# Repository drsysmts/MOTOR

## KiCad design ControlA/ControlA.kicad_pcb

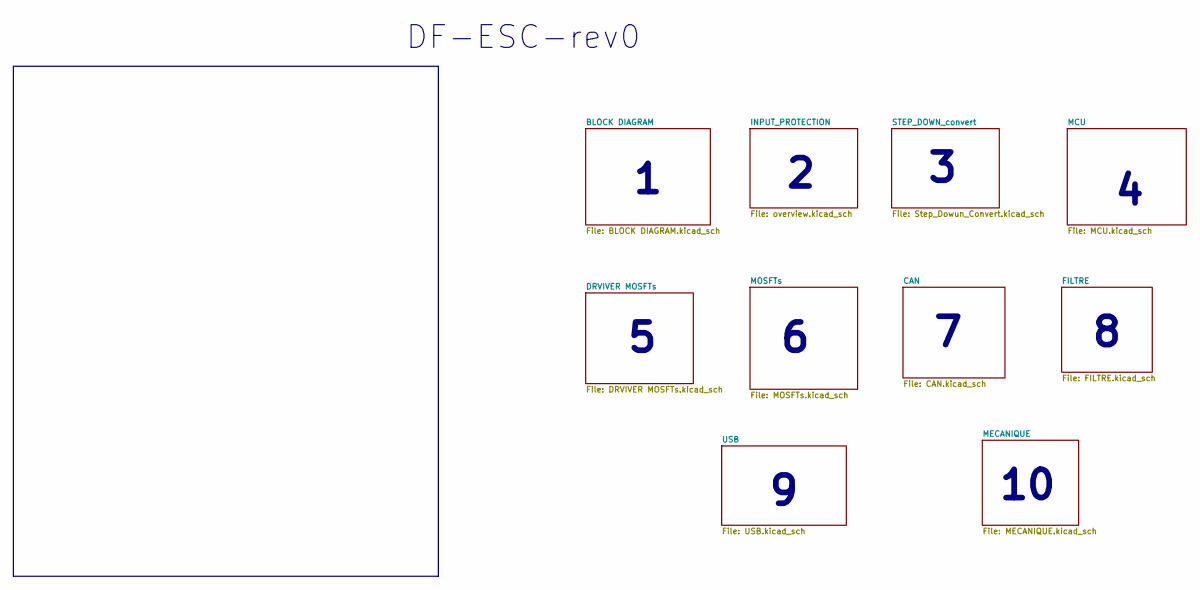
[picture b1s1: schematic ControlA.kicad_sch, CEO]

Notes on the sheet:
DF-ESC-rev0

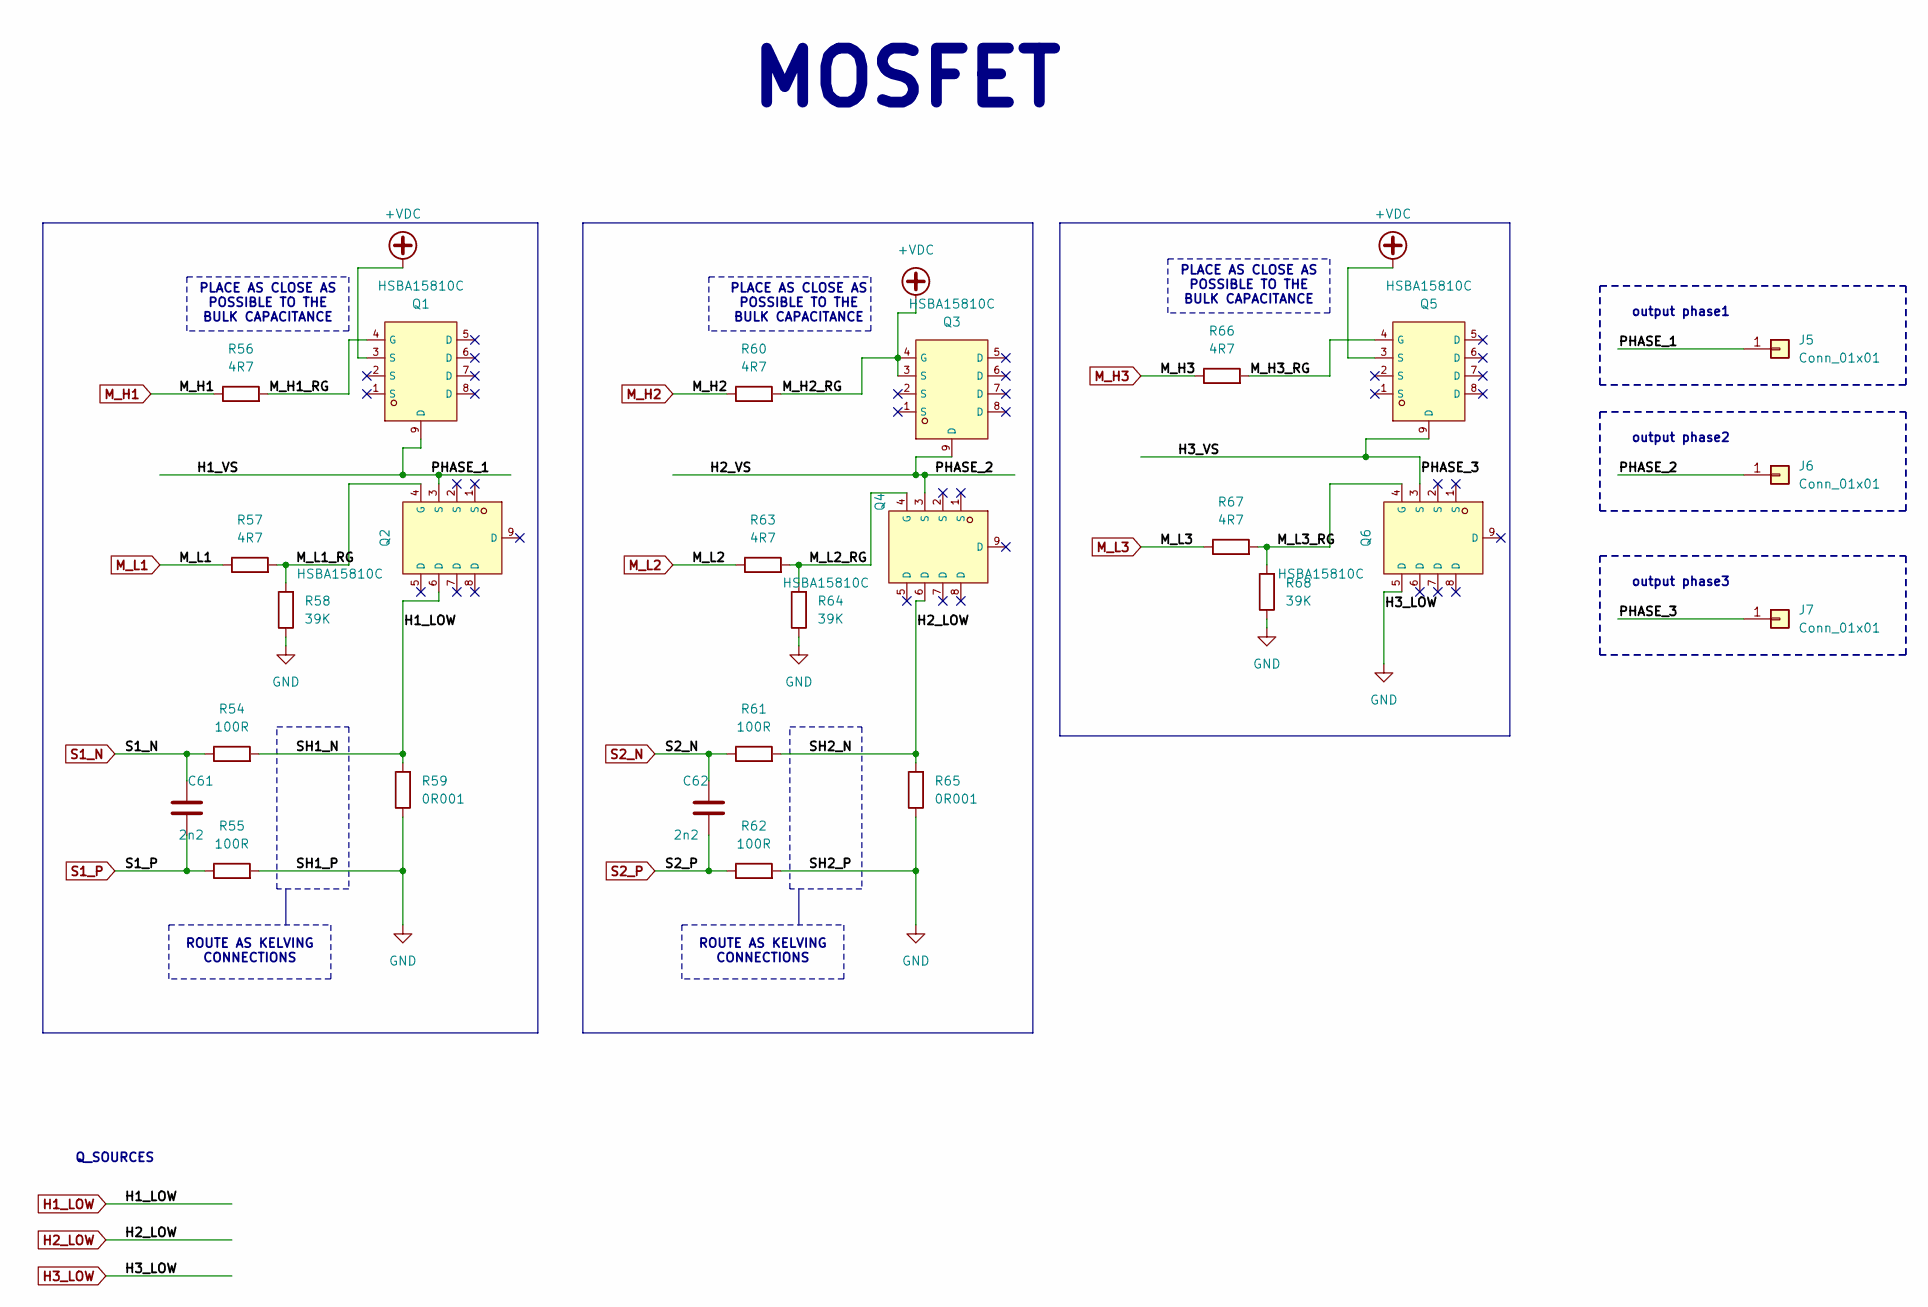
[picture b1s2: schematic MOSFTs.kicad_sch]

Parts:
C61, C62: 2n2; C_0603_1608Metric
J5, J6, J7: Conn_01x01; 7461097
Q1, Q2, Q3, Q4, Q5, Q6: HSBA15810C; PQFN-8_L6.0-W5.0-P1.27-LS6.0-BL; LCSC C845605
R54, R55, R61, R62: 100R; R_0805_2012Metric
R56, R57, R60, R63, R66, R67: 4R7; R_0805_2012Metric
R58, R64, R68: 39K; R_0805_2012Metric
R59, R65: 0R001; R_0805_2012Metric

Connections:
+VDC: Q1.3 (S), Q3.3 (S), Q3.4 (G), Q5.3 (S), R60.2; also elsewhere on the board
/MOSFTs/H1_VS: J5.1, Q1.9 (D), Q2.3 (S)
/MOSFTs/H2_VS: J6.1, Q3.9 (D), Q4.3 (S)
/MOSFTs/H3_VS: J7.1, Q5.9 (D), Q6.3 (S)
/MOSFTs/M_H1_RG: Q1.4 (G), R56.2
/MOSFTs/M_H3_RG: Q5.4 (G), R66.2
/MOSFTs/M_L1_RG: Q2.4 (G), R57.2, R58.2
/MOSFTs/M_L2_RG: Q4.4 (G), R63.2, R64.2
/MOSFTs/M_L3_RG: Q6.4 (G), R67.2, R68.2
H1_LOW: Q2.6 (D), R54.2, R59.2; also elsewhere on the board
H2_LOW: Q4.6 (D), R61.2, R65.2; also elsewhere on the board
H3_LOW: Q6.5 (D), R55.2, R58.1, R59.1, R62.2, R64.1, R65.1, R68.1; also elsewhere on the board
M_H1: R56.1; also elsewhere on the board
M_H2: R60.1; also elsewhere on the board
M_H3: R66.1; also elsewhere on the board
M_L1: R57.1; also elsewhere on the board
M_L2: R63.1; also elsewhere on the board
M_L3: R67.1; also elsewhere on the board
S1_N: C61.1, R54.1; also elsewhere on the board
S1_P: C61.2, R55.1; also elsewhere on the board
S2_N: C62.1, R61.1; also elsewhere on the board
S2_P: C62.2, R62.1; also elsewhere on the board

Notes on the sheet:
PLACE AS CLOSE AS POSSIBLE TO THE BULK CAPACITANCE
ROUTE AS KELVING CONNECTIONS
output phase2
output phase3
output phase1
MOSFET
Q_SOURCES

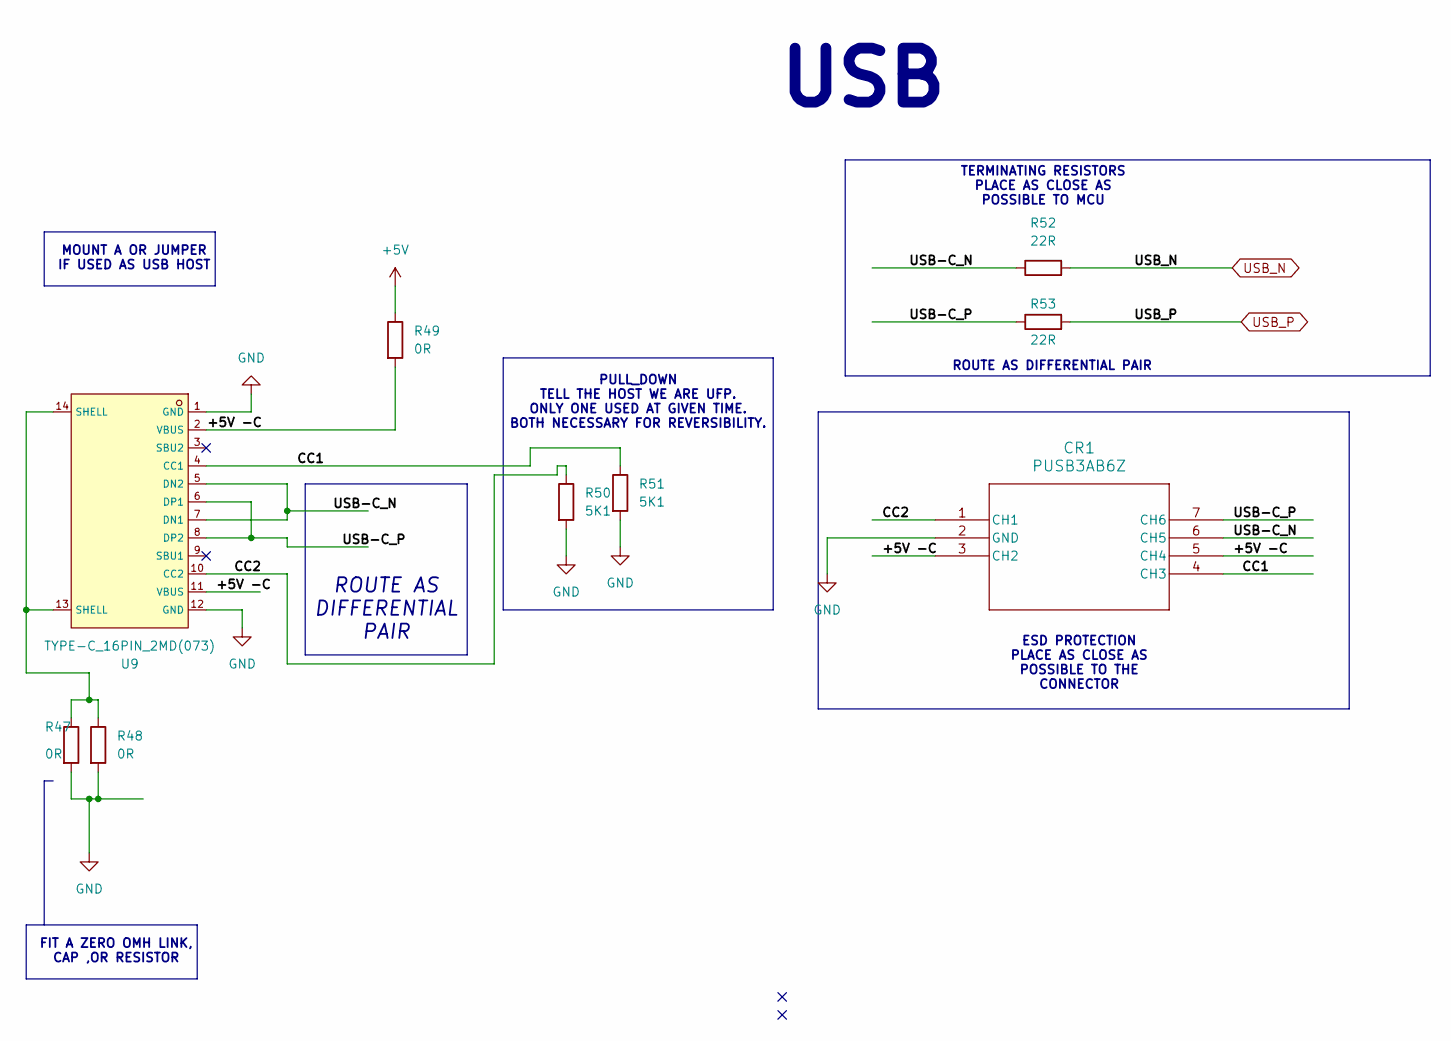
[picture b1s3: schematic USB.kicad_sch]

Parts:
CR1: PUSB3AB6Z; PUSB3AB6Z_NEX-M
R47, R48, R49: 0R; R_0805_2012Metric
R50, R51: 5K1; R_0805_2012Metric
R52, R53: 22R; R_0805_2012Metric
U9: TYPE-C_16PIN_2MD(073); USB-C-SMD_TYPE-C-6PIN-2MD-073; LCSC C2765186

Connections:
+5V: R49.1; also elsewhere on the board
/USB/+5V -C: CR1.3 (CH2), CR1.5 (CH4), R49.2, U9.2 (VBUS), U9.11 (VBUS)
/USB/CC1: CR1.4 (CH3), R51.1, U9.4 (CC1)
/USB/CC2: CR1.1 (CH1), R50.1, U9.10 (CC2)
/USB/USB-C_N: CR1.6 (CH5), R52.1, U9.5 (DN2), U9.7 (DN1)
/USB/USB-C_P: CR1.7 (CH6), R53.1, U9.6 (DP1), U9.8 (DP2)
H3_LOW: CR1.2 (GND), R47.2, R48.2, R50.2, R51.2, U9.1 (GND), U9.12 (GND); also elsewhere on the board
unnamed: R47.1, R48.1, U9.13 (SHELL), U9.14 (SHELL)
USB_N: R52.2; also elsewhere on the board
USB_P: R53.2; also elsewhere on the board

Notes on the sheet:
ROUTE AS DIFFERENTIAL PAIR
MOUNT A OR JUMPER IF USED AS USB HOST
FIT A ZERO OMH LINK, CAP ,OR RESISTOR
ROUTE AS DIFFERENTIAL PAIR
TERMINATING RESISTORS PLACE AS CLOSE AS POSSIBLE TO MCU
PULL_DOWN TELL THE HOST WE ARE UFP. ONLY ONE USED AT GIVEN TIME. BOTH NECESSARY FOR REVERSIBILITY.
ESD PROTECTION PLACE AS CLOSE AS POSSIBLE TO THE CONNECTOR
USB

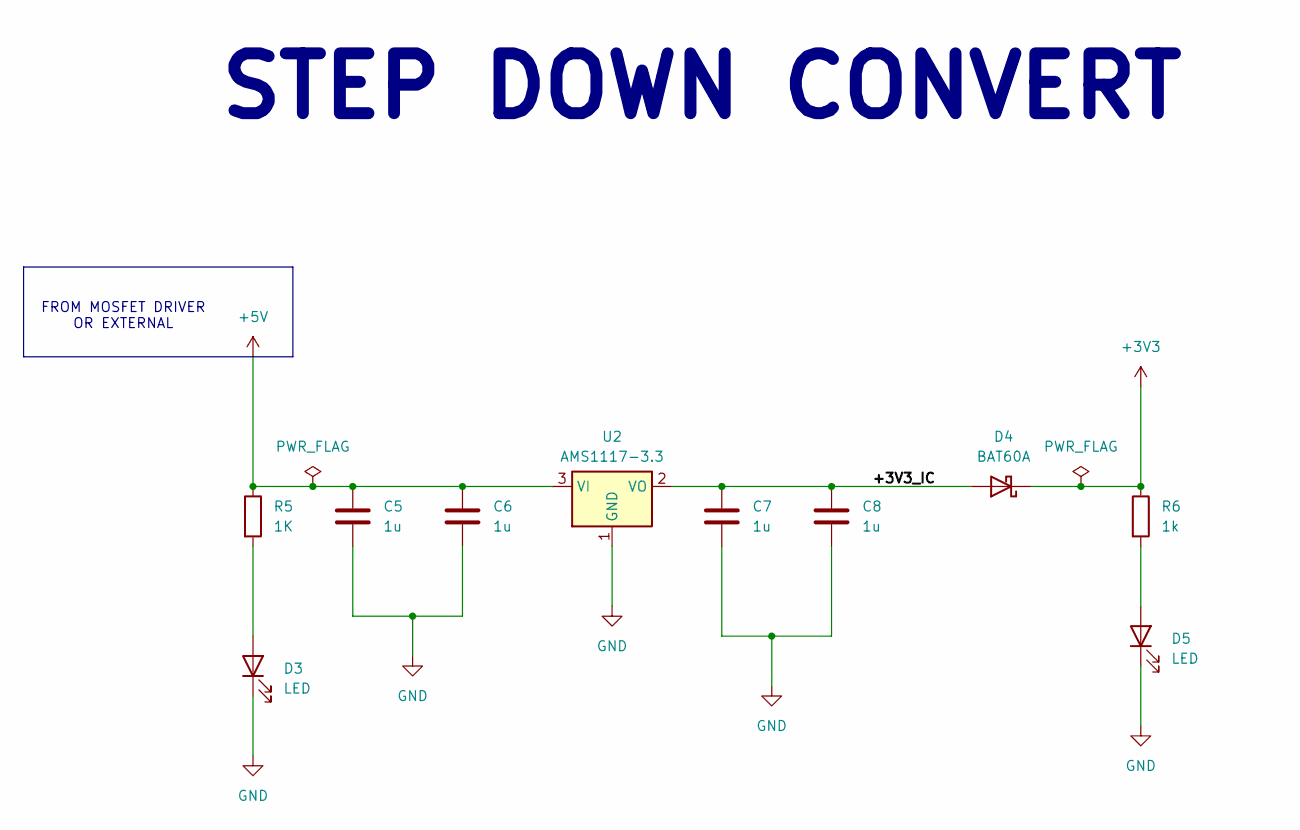
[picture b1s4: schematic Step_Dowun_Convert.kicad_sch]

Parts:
C5, C6, C7, C8: 1u; C_0603_1608Metric
D3, D5: LED; LED0805-R-RD
D4: BAT60A; D_SOD-323
R5: 1K; R_0805_2012Metric
R6: 1k; R_0805_2012Metric
U2: AMS1117-3.3; SOT-223-3_TabPin2

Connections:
+3V3: D4.1 (K), R6.1; also elsewhere on the board
+5V: C5.1, C6.1, R5.1, U2.3 (VI); also elsewhere on the board
/STEP_DOWN_convert/+3V3_IC: C7.1, C8.1, D4.2 (A), U2.2 (VO)
H3_LOW: C5.2, C6.2, C7.2, C8.2, D3.1 (K), D5.1 (K), U2.1 (GND); also elsewhere on the board
unnamed: D3.2 (A), R5.2
unnamed: D5.2 (A), R6.2

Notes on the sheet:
FROM MOSFET DRIVER OR EXTERNAL
STEP DOWN CONVERT

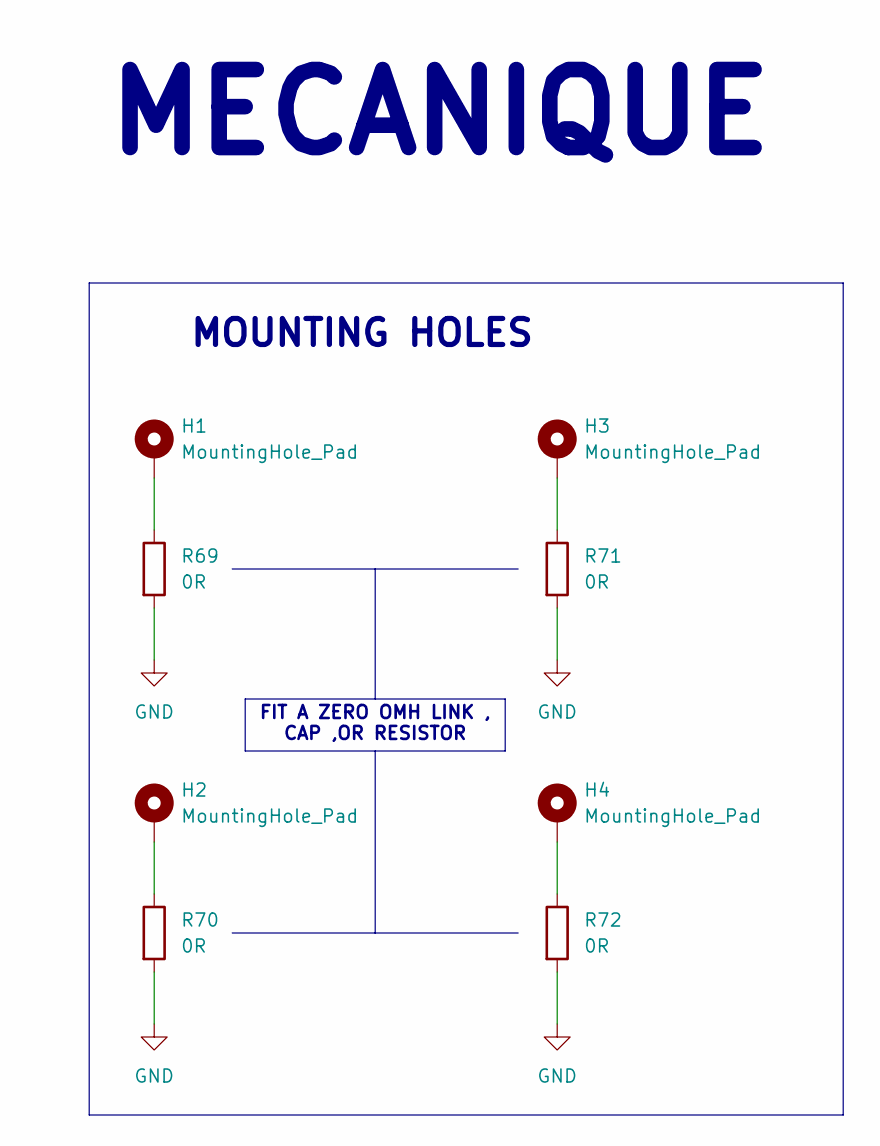
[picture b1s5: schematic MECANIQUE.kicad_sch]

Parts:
H1, H2, H3, H4: MountingHole_Pad; MountingHole_4.3mm_M4_Pad_Via
R69, R70, R71, R72: 0R; R_0805_2012Metric

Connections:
H3_LOW: R69.2, R70.2, R71.2, R72.2; also elsewhere on the board
unnamed: H1.1, R69.1
unnamed: H2.1, R70.1
unnamed: H3.1, R71.1
unnamed: H4.1, R72.1

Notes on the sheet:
MECANIQUE
MOUNTING HOLES
FIT A ZERO OMH LINK , CAP ,OR RESISTOR

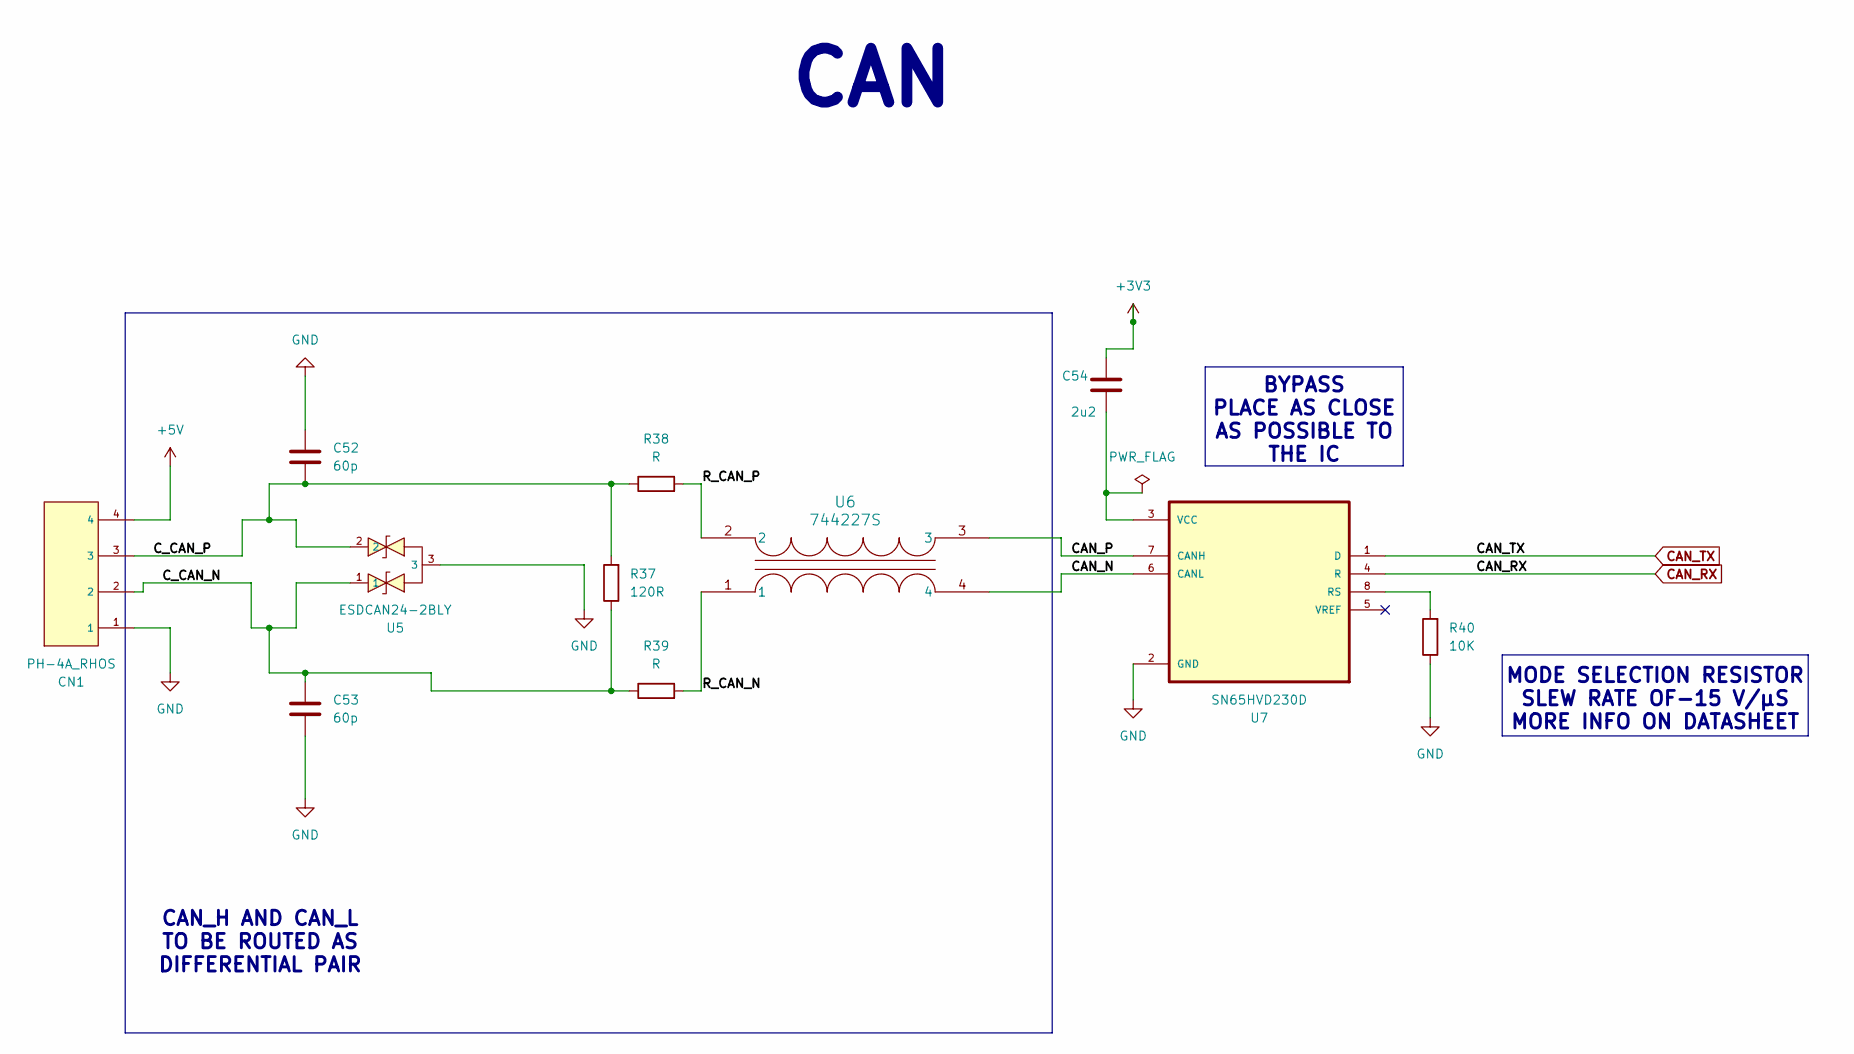
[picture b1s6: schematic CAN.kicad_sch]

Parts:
C52, C53: 60p; C_0603_1608Metric
C54: 2u2; C_0603_1608Metric
CN1: PH-4A_RHOS; CONN-TH_PH-4A; LCSC C2321
R37: 120R; R_0805_2012Metric
R38, R39: R; R_0805_2012Metric
R40: 10K; R_0805_2012Metric
U5: ESDCAN24-2BLY; SOT-23-3_L3.0-W1.7-P0.95-LS2.9-BR; LCSC C246766
U6: 744227S; SMD_227S_WRE-M
U7: SN65HVD230D; SOIC127P599X175-8N

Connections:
+3V3: C54.1; also elsewhere on the board
+5V: CN1.4; also elsewhere on the board
/CAN/CAN_N: U6.4, U7.6 (CANL)
/CAN/CAN_P: U6.3, U7.7 (CANH)
/CAN/C_CAN_N: C53.1, CN1.2, R37.1, R39.1, U5.1
/CAN/C_CAN_P: C52.2, CN1.3, R37.2, R38.1, U5.2
/CAN/R_CAN_N: R39.2, U6.1
/CAN/R_CAN_P: R38.2, U6.2
CAN_RX: U7.4 (R); also elsewhere on the board
CAN_TX: U7.1 (D); also elsewhere on the board
H3_LOW: C52.1, C53.2, CN1.1, R40.1, U5.3, U7.2 (GND); also elsewhere on the board
unnamed: R40.2, U7.8 (RS)
unnamed: C54.2, U7.3 (VCC)

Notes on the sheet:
CAN_H AND CAN_L TO BE ROUTED AS DIFFERENTIAL PAIR
CAN
BYPASS PLACE AS CLOSE AS POSSIBLE TO THE IC
MODE SELECTION RESISTOR SLEW RATE OF-15 V/µS MORE INFO ON DATASHEET

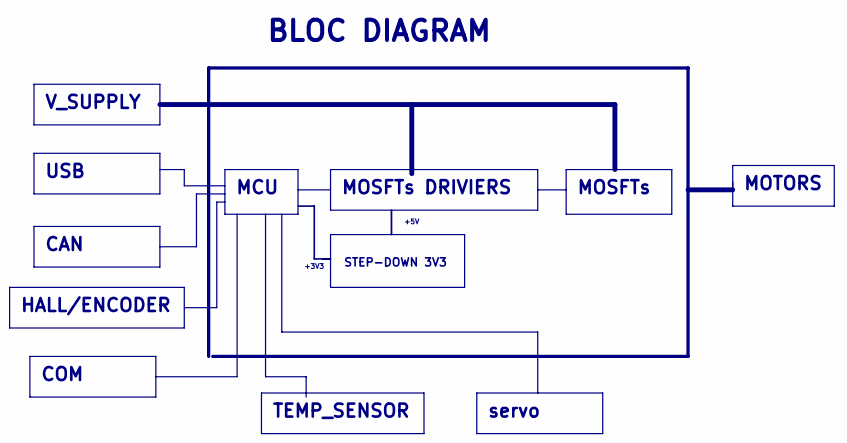
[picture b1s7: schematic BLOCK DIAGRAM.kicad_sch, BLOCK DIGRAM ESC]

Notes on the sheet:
MOSFTs DRIVIERS
CAN
TEMP_SENSOR
HALL/ENCODER
COM
MOTORS
servo
USB
MCU
MOSFTs
V_SUPPLY
+3V3
BLOC DIAGRAM
STEP-DOWN 3V3
+5V

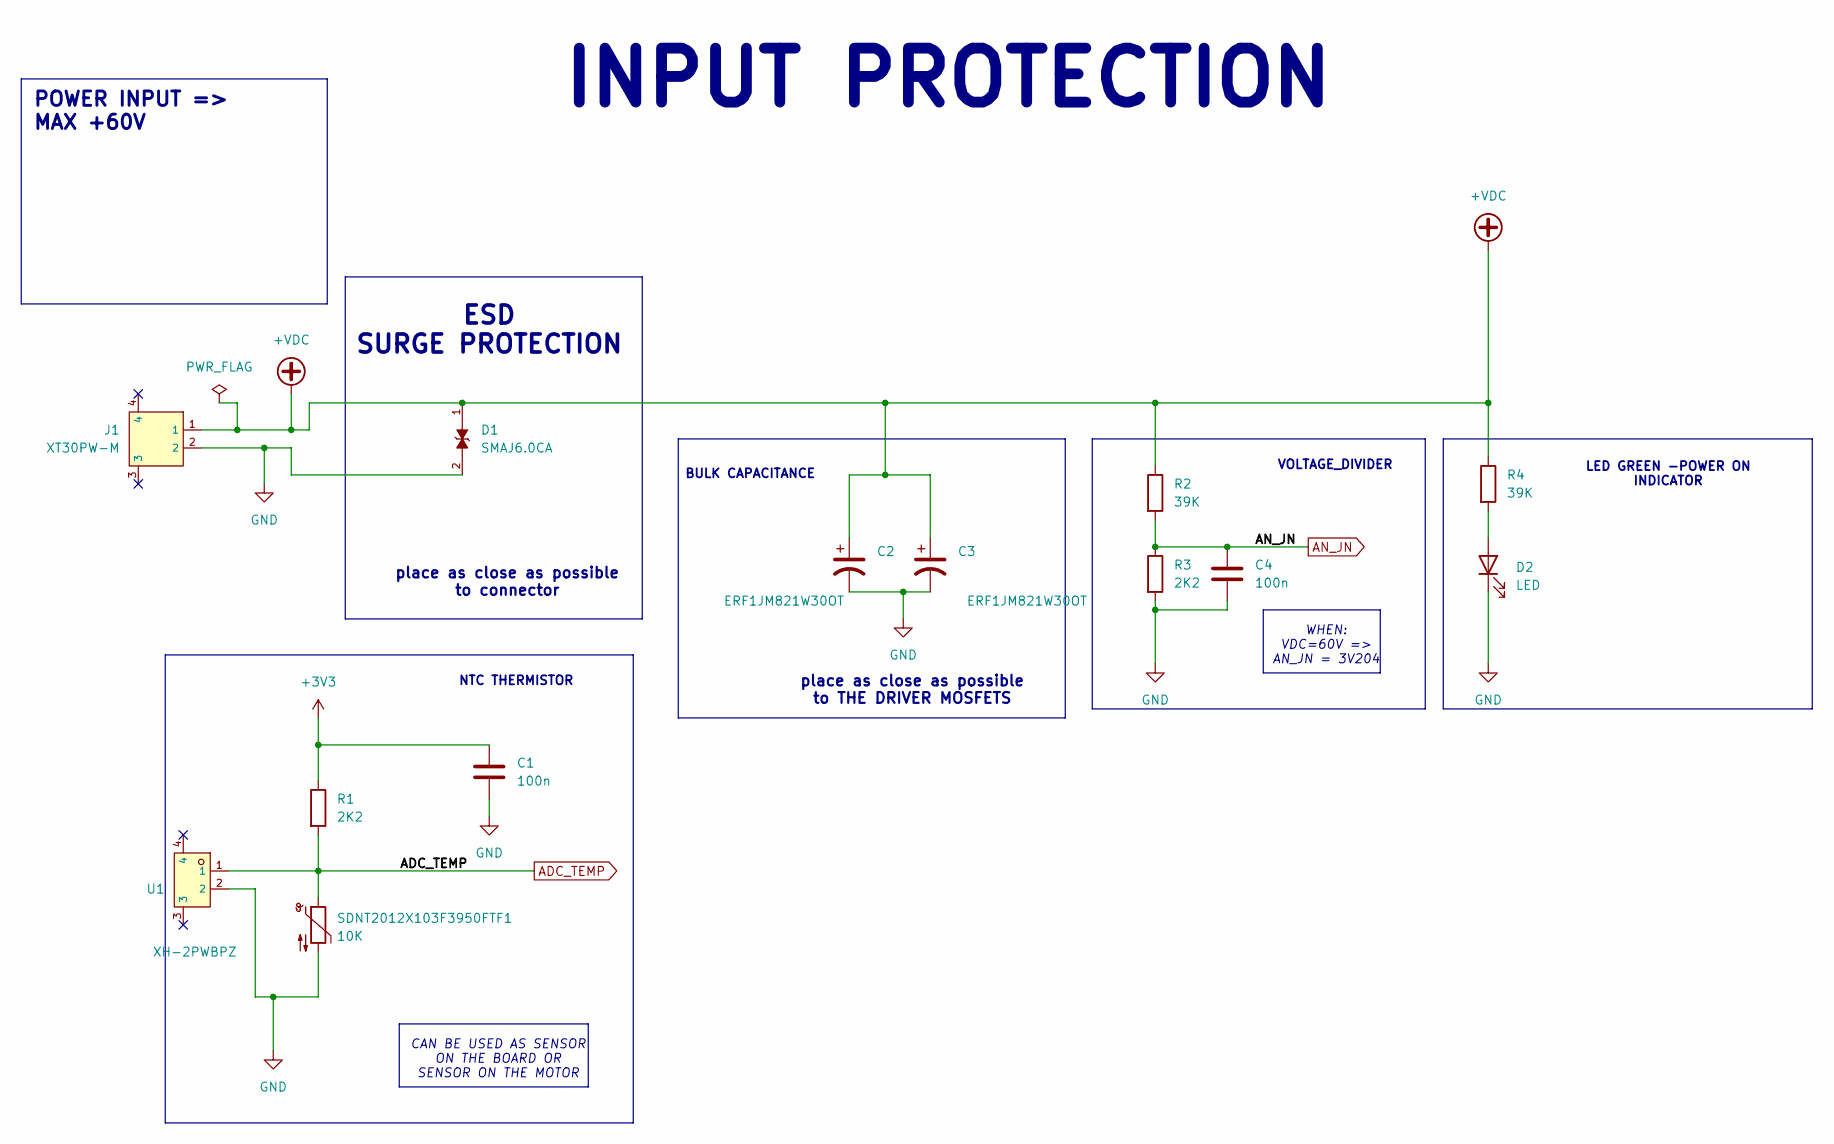
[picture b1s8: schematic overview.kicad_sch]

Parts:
C1: 100n; C_0805_2012Metric
C2, C3: ERF1JM821W30OT; CP_Radial_D12.5mm_P5.00mm
C4: 100n; C_0603_1608Metric
D1: SMAJ6.0CA; DIOM4325X250N; PARTREV S2102
D2: LED; LED0805-R-RD
J1: XT30PW-M; CONN-TH_XT30PW-M; PARTREV 1.2; LCSC C431092
R1, R3: 2K2; R_0805_2012Metric
R2, R4: 39K; R_0805_2012Metric
SDNT2012X103F3950FTF1: 10K; R_0805_2012Metric
U1: XH-2PWBPZ; CONN-SMD_XH-2PWBPZ; LCSC C2687444

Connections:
+3V3: C1.1, R1.1; also elsewhere on the board
+VDC: C2.1, C3.1, D1.1, J1.1, R2.1, R4.1; also elsewhere on the board
ADC_TEMP: R1.2, SDNT2012X103F3950FTF1.1, U1.1
AN_JN: C4.1, R2.2, R3.1
H3_LOW: C1.2, C2.2, C3.2, C4.2, D1.2, D2.1 (K), J1.2, R3.2, SDNT2012X103F3950FTF1.2, U1.2; also elsewhere on the board
unnamed: D2.2 (A), R4.2

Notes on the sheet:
POWER INPUT => MAX +60V
LED GREEN -POWER ON INDICATOR
place as close as possible to connector
ESD SURGE PROTECTION
NTC THERMISTOR
VOLTAGE_DIVIDER
CAN BE USED AS SENSOR ON THE BOARD OR SENSOR ON THE MOTOR
place as close as possible to THE DRIVER MOSFETS
BULK CAPACITANCE
INPUT PROTECTION
WHEN: VDC=60V => AN_JN = 3V204

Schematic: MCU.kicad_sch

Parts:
C9, C10: 100n; C_0603_1608Metric
C11, C12: 10p; C_0603_1608Metric
C13, C14, C15, C16, C17, C18, C20, C22, C23, C24, C25: 100n; C_0402_1005Metric
C19, C21: 2u2; C_0603_1608Metric
D6, D7, D8: LED; LED0805-R-RD
FB1: 120R; L0603
J2: Conn_01x08; PinHeader_1x08_P1.00mm_Vertical
J3: Conn_01x06; PinHeader_1x06_P1.00mm_Vertical
J4: Conn_01x03; PinHeader_1x03_P1.00mm_Vertical
R7: 39K; R_0805_2012Metric
R8, R15, R16: 2K2; R_0805_2012Metric
R9, R14: 0R; R_0805_2012Metric
R10, R11: 0R; R_0402_1005Metric
R12, R13: 1K; R_0805_2012Metric
SDNT2012X103F3950FTF2: 10K; R_0805_2012Metric
SW1: TS-KG87S-AT15F; SW-SMD_4P-L5.2-W5.2-P3.70-LS6.4; LCSC C2874421
U3: STM32F405RGTx; LQFP-64_10x10mm_P0.5mm
Y1: Crystal; Crystal_SMD_5032-2Pin_5.0x3.2mm

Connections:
+3V3: C10.1, C13.1, C14.1, C15.1, C16.1, C17.1, C18.1, C25.1, FB1.2, J2.2, J3.1, R9.2, R14.1, SDNT2012X103F3950FTF2.1, U3.1 (VBAT), U3.19 (VDD), U3.32 (VDD), U3.48 (VDD), U3.64 (VDD); also elsewhere on the board
+5V: J2.1, J4.1; also elsewhere on the board
+VDC: R7.2; also elsewhere on the board
/MCU/ADC_TEMP: R16.2, SDNT2012X103F3950FTF2.2, U3.17 (PA3)
/MCU/AN_JN: C9.1, R7.1, R8.2, U3.10 (PC2)
/MCU/BOOT0_P: R14.2, U3.60 (BOOT0)
/MCU/LED_GREEN: R12.2, U3.24 (PC4)
/MCU/LED_RED: R13.2, U3.25 (PC5)
/MCU/MISQ_ADC_EXT2: J2.7, U3.22 (PA6)
/MCU/NRST: C20.1, J3.5, SW1.3, SW1.4, U3.7 (NRST)
/MCU/PH_0: C11.1, R10.1, Y1.1
/MCU/PH_0_P: R10.2, U3.5 (PH0)
/MCU/PH_1: C12.1, R11.1, Y1.2
/MCU/PH_1_P: R11.2, U3.6 (PH1)
/MCU/SCK_ADC_EXT: J2.4, U3.21 (PA5)
/MCU/SERVO: C24.2, R15.1, U3.57 (PB5)
/MCU/SWCLK: J3.2, U3.49 (PA14)
/MCU/SWDIO: J3.4, U3.46 (PA13)
/MCU/VCAP_1: C19.1, U3.31 (VCAP_1)
/MCU/VCAP_2: C21.1, U3.47 (VCAP_2)
BR_SO1: U3.26 (PB0); also elsewhere on the board
BR_SO2: U3.27 (PB1); also elsewhere on the board
CAN_RX: U3.61 (PB8); also elsewhere on the board
CAN_TX: U3.62 (PB9); also elsewhere on the board
DC_CAL: U3.33 (PB12); also elsewhere on the board
EN_GATE: U3.51 (PC10); also elsewhere on the board
FAULT: U3.53 (PC12); also elsewhere on the board
H1: U3.43 (PA10); also elsewhere on the board
H2: U3.42 (PA9); also elsewhere on the board
H3: U3.41 (PA8); also elsewhere on the board
H3_LOW: C9.2, C10.2, C11.2, C12.2, C13.2, C14.2, C15.2, C16.2, C17.2, C18.2, C19.2, C20.2, C21.2, C22.2, C23.2, C24.1, C25.2, D6.1 (K), D7.1 (K), D8.1 (K), J2.3, J2.8, J3.3, J4.2, R8.1, R16.1, SW1.1, SW1.2, U3.12 (VSSA), U3.18 (VSS), U3.63 (VSS); also elsewhere on the board
HALL1_OUT: U3.58 (PB6); also elsewhere on the board
HALL2_OUT: U3.59 (PB7); also elsewhere on the board
HALL3_OUT: U3.52 (PC11); also elsewhere on the board
L1: U3.36 (PB15); also elsewhere on the board
L2: U3.35 (PB14); also elsewhere on the board
L3: U3.34 (PB13); also elsewhere on the board
unnamed: D6.2 (A), R9.1
unnamed: D7.2 (A), R12.1
unnamed: D8.2 (A), R13.1
unnamed: J4.3, R15.2
unnamed: C22.1, C23.1, FB1.1, U3.13 (VDDA)
RX_SCL_MOSI: J2.6, U3.23 (PA7), U3.29 (PB10), U3.38 (PC7)
SENSE1: U3.16 (PA2); also elsewhere on the board
SENSE2: U3.15 (PA1); also elsewhere on the board
SENSE3: U3.14 (PA0); also elsewhere on the board
TEMP_MOTOR: U3.8 (PC0); also elsewhere on the board
TX_SDA_NSS: J2.5, U3.20 (PA4), U3.30 (PB11), U3.37 (PC6)
USB_N: U3.44 (PA11); also elsewhere on the board
USB_P: U3.45 (PA12); also elsewhere on the board

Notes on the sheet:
COMMUNICATION
NTC THERMOSATA
SERVO
PROGRAMMING/DEBUG
See Boot Modes Table 7
voltage divider
SUBTITUE WITH 100R IF USED WITH AS SERVO OUTPUT
WHEN: VDC =60V=> AN_JN=3V204

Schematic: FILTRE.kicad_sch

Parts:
C55, C56, C57: 4n7; C_0603_1608Metric
C58, C59, C60: 100n; C_0603_1608Metric
R41, R42, R43: 2K2; R_0805_2012Metric
R44, R45, R46: 10K; R_0805_2012Metric
U8: B06B-PARK-1_(LF)(SN); CONN-TH_B06B-PARK-1-LF-SN; LCSC C161720

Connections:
+3V3: C58.1, C59.1, C60.1, R41.1, R42.1, R43.1; also elsewhere on the board
+5V: U8.6; also elsewhere on the board
/FILTRE/HALL_1_IN: R44.1, U8.4
/FILTRE/HALL_2_IN: R45.1, U8.3
/FILTRE/HALL_3_IN: R46.1, U8.2
H3_LOW: C55.2, C56.2, C57.2, C58.2, C59.2, C60.2, U8.1; also elsewhere on the board
HALL1_OUT: R44.2; also elsewhere on the board
HALL2_OUT: R45.2; also elsewhere on the board
HALL3_OUT: R46.2; also elsewhere on the board
unnamed: C55.1, R41.2
unnamed: C56.1, R42.2
unnamed: C57.1, R43.2
TEMP_MOTOR: U8.5; also elsewhere on the board

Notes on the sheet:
Hall_1 FILTRE
Hall_3 FILTRE
TO MCU =>
Hall_2 FILTRE
HALL ENCODER OUTPUT
FILTRE
HALL ENCODER INPUT

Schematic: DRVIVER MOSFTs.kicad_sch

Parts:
C26, C27, C28, C43: 100n; C_0603_1608Metric
C29, C30, C31, C39, C46, C48: 10u; C_0603_1608Metric
C32: 0.022u; C_0603_1608Metric
C33, C40, C41, C42, C44, C45: 1u; C_0603_1608Metric
C34: 6800p; C_0603_1608Metric
C35: 120p; C_0603_1608Metric
C36, C37, C38, C47: 2.2u; C_0603_1608Metric
D10: PMEG6020; SOD-123_L2.8-W1.8-LS3.7-RD
D14: BAT60A; D_SOD-323
R17: 18k; R_0805_2012Metric
R18: 3k3; R_0805_2012Metric
R27: 16K2; R_0805_2012Metric
R28: 10K; R_0805_2012Metric
R29: 250k; R_0805_2012Metric
R30: 1M; R_0805_2012Metric
R31, R33, R35: 34K8; R_0805_2012Metric
R32, R34, R36: 4k99; R_0805_2012Metric
U4: DRV8302DCAR; DCA56_6P35X3P61-M
U10: YSPI0530-220M; IND-SMD_L5.4-W5.2-YSPI0530-220M; LCSC C718383

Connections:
+3V3: U4.9 (M_OC), U4.24 (REF); also elsewhere on the board
+5V: D14.1 (K); also elsewhere on the board
+VDC: C29.1, C33.1, C40.1, C41.1, C42.1, C44.1, C45.1, C46.1, C48.1, U4.29 (PVDD1), U4.53 (PVDD2), U4.54 (PVDD2); also elsewhere on the board
/DRVIVER MOSFTs/BST_A: C26.1, U4.48 (BST_A)
/DRVIVER MOSFTs/BST_B: C27.1, U4.43 (BST_B)
/DRVIVER MOSFTs/BST_BK: C43.1, U4.52 (BST_BK)
/DRVIVER MOSFTs/BST_C: C28.1, U4.38 (BST_C)
/DRVIVER MOSFTs/COMP: C35.1, R27.1, U4.2 (COMP)
/DRVIVER MOSFTs/CP1: C32.2, U4.14 (CP1)
/DRVIVER MOSFTs/CP2: C32.1, U4.15 (CP2)
/DRVIVER MOSFTs/DTC: R28.2, U4.7 (DTC)
/DRVIVER MOSFTs/GVDD: C36.1, C47.1, U4.13 (GVDD)
/DRVIVER MOSFTs/OC_ADJ: C37.2, U4.11 (OC_ADJ)
/DRVIVER MOSFTs/PH: C43.2, D10.2 (K), U4.50 (PH), U4.51 (PH), U10.1
/DRVIVER MOSFTs/RT_CLK: R29.2, U4.1 (RT_CLK)
/DRVIVER MOSFTs/VSENSE: R17.1, R18.2, U4.3 (VSENSE)
BR_SO1: U4.25 (SO1); also elsewhere on the board
BR_SO2: U4.26 (SO2); also elsewhere on the board
DC_CAL: U4.12 (DC_CAL); also elsewhere on the board
EN_GATE: U4.16 (EN_GATE); also elsewhere on the board
FAULT: U4.6 (*FAULT); also elsewhere on the board
H1: U4.17 (INH_A); also elsewhere on the board
H1_LOW: U4.44 (SL_A); also elsewhere on the board
H1_VS: C26.2, R31.2, U4.46 (SH_A)
H2: U4.19 (INH_B); also elsewhere on the board
H2_LOW: U4.39 (SL_B); also elsewhere on the board
H2_VS: C27.2, R35.2, U4.41 (SH_B)
H3: U4.21 (INH_C); also elsewhere on the board
H3_LOW: C29.2, C30.2, C31.2, C33.2, C34.2, C35.2, C36.2, C37.1, C38.1, C39.2, C40.2, C41.2, C42.2, C44.2, C45.2, C46.2, C47.2, C48.2, D10.1 (A), R18.1, R28.1, R29.1, R30.2, R32.1, R34.1, R36.1, U4.8 (M_PWM), U4.10 (GAIN), U4.23 (DVDD), U4.28 (AGND), U4.34 (SL_C), U4.57 (GND); also elsewhere on the board
H3_VS: C28.2, R33.2, U4.36 (SH_C)
L1: U4.18 (INL_A); also elsewhere on the board
L2: U4.20 (INL_B); also elsewhere on the board
L3: U4.22 (INL_C); also elsewhere on the board
M_H1: U4.47 (GH_A); also elsewhere on the board
M_H2: U4.42 (GH_B); also elsewhere on the board
M_H3: U4.37 (GH_C); also elsewhere on the board
M_L1: U4.45 (GL_A); also elsewhere on the board
M_L2: U4.40 (GL_B); also elsewhere on the board
M_L3: U4.35 (GL_C); also elsewhere on the board
unnamed: C34.1, R27.2
unnamed: C30.1, C31.1, C39.1, D14.2 (A), R17.2, U10.2
unnamed: C38.2, U4.27 (AVDD)
unnamed: R30.1, U4.49 (BIAS)
S1_N: U4.33 (SN1); also elsewhere on the board
S1_P: U4.32 (SP1); also elsewhere on the board
S2_N: U4.31 (SN2); also elsewhere on the board
S2_P: U4.30 (SP2); also elsewhere on the board
SENSE1: R31.1, R32.2; also elsewhere on the board
SENSE2: R35.1, R36.2; also elsewhere on the board
SENSE3: R33.1, R34.2; also elsewhere on the board

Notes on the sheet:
KEEP AWAY FROM NOISY TRACKS AND COMPONENTS
OUTPUT PORTS
PHASE_1
INPUT PORT
PHASE_2
SENSE 2 -PHASE 2
MOSFET DRIVER
SENSE 1 -PHASE 1
PHASE_3

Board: 4 copper layers, 167 parts (0 on the bottom side), 120 nets, no tracks yet.

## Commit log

2024-06-20 Add .gitattributes file to manage line endings
2024-06-20 Normalize line endings
2024-06-22 add libray symbole and add sheet
2024-06-22 shema input protection final
2024-06-22 usb control
2024-06-29 final shema symbole
2024-06-29 test0
    FIREST
2024-06-30 start placement compentent
2024-07-10 CHANGE V11
    change v1
2024-07-10 connector
    add conctor power mosft
2024-07-11 net change
    change net
2024-07-12 layout
    layout mcu
2024-07-16 update
    update layout
2024-07-19 cheek change
    check change
2024-07-26 upta new layer
    updute new layer cheek cpaictor change from bttom side to front
2024-08-06 change in shama
    change schema and lyout
2024-08-06 change layour boedrer
    change layout broder
